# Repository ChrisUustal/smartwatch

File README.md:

# DataRacer
### A Wrist-Mounted Data Logger for Race Car Drivers
###### By Chris Uustal | Fall '21 | CE395 - Wearables & Embedded Computing
## Executive Summary:
#### Motivation: Why am I doing this? 
I'm taking a class (duh). But actually, I'm a member of the Formula SAE team here
at Northwestern University, and we've spent years collecting data on our vehicle
while never collecting data on our drivers. I wanted to change that. 
#### Problem: What am I fixing? 
Collecting meaningful data from a driver is HARD. They need to wear a very particular
racing suit and the environment they are operating in is... less than forgiving. The
solution also has to be very user friendly and reliable, because if it isn't then
they just won't use it. 
#### Solution: How am I fixing it? 
I designed a smart watch platform capable of collecting and logging sensor data that
has a simple user interface, logs data to a removable microSD card, and can be easily
scaled to include whatever sensors are needed by the driver (whenever those sensors
are back in stock). 
#### Impact: The bigger picture 
The team spends thousands of hours every year trying to tune every ounce of performance 
out of our vehicle, but the driver is picked based off knowledge--not skill. If 
we can find meaningful ways to improve the skills of our drivers based off this data,
then that could make bigger improvements to the performance of our vehicle than some 
projects ever could. 
## Design: 
#### Visual Story

#### Hardware Block Diagram

#### What parts did I use? 
- ESP32 Feather by Adafruit
- OLED 128x64 FeatherWing by Adafruit
- MicroSD Breakout Board by Adafruit
- MPU6050 9DOF+Temp I2C Sensor (unknown vendor)
- 500mAh LiPoly Battery by Adafruit
#### Implementation
###### Hardware 
The decision was made early on to use parts that were as easy as possible to get working 
out of the box with as little tinkering as possible. Both Sparkfun and Adafruit have 
fantastic development platforms for this, so I arbitrarily chose Adafruit, since they both
appeared to have similar levels of hardware diversity. With that, I immediately began 
moving forward with the Adafruit ESP32 Huzzah feather and OLED 128x32 FeatherWing as my 
MCU and interface of choice. I've worked with the ESP32 previously and was quite happy 
with its performance and feature set, so I saw no reason to reinvent the wheel. The only
major downside of the ESP32 compared to alternative options is its high power draw, but
since this design was for prototyping only, I wasn't as concerned about battery life so 
long as it doesn't completely destroy the demo experience, which ended up being a good choice. 
The OLED 128x32 FeatherWing (which I later upgraded to the 128x64 variant) offered interface
buttons and a screen for displaying information to the user, so it checked all my interface 
requirements in one package. Since all featherWings are intended to be stacking shields 
directly on top of any feather MCU, I implemented it as such, directly stacking the display
ontop of the MCU even in the final package. Conventionally the two components would be spaced 
out by male headers on the OLED plugged into female headers from the ESP32, but this takes
up a lot of vertical space within my packaging, something which was already at a premium 
in the tiny form factor I was going for. As such, in the final build I actually soldered
both the ESP32 and OLED directly to the same pair of male headers, allowing them to be stacked 
together in a package nearly 0.25 inches shorter than with conventional stacking. The
buttons integrated into the OLED directly map to GPIO ports on the ESP32, and the OLED 
gets its display information over I2C. The OLED comes with a library and tutorial out of
the box, so it was up and running in no time. 
<br /><br />
For the battery, Adafruit offers a selection of LiPoly batteries that are capable
of directly interfacing with and charging from the ESP32 feather, so I used the largest one
from their series capable of fitting into the footprint I ended up deciding on, 500mAh. I
originally worked with a 1200mAh battery, but this ended up being significantly larger than
was reasonable for a wrist-mounted device. 
<br /><br />
The MicroSD card breakout that I used was the only one Adafruit offered, so since I'd already
had good luck on their other products, I simply continued using them as my vendor of choice. 
It included 5v to 3.3v level shifting, so while that made the package a little larger, it
also protected me in case I ended up wanting to use the breakout in another design later 
on (which I didn't end up doing, but that's fine). It interfaced over SPI, which is expected
for a MicroSD card, but it also offered some nice quality of life features like card detection
and an indicator LED when it's being written to. 
<br /><br />
The only actual sensor in the device, the MPU6050 9DOF+Temp sensor I just happened to
have already in inventory, so I started testing with it originally just to have an example
sensor without the intention of actually including it in the final product. It isn't from
Adafruit and honestly I don't even know where I got it from, but it also operated off I2C 
and worked easily enough that I didn't ever have to worry about it. It was even small enough 
that it never presented any major packaging issues. 
<br /><br />
I wanted to include a lot more sensors in the design, but part shortage issues as well as
some miscommunications with the university buying some sensors for me ended up making it 
more logically to just focus on developing the backbone system and leaving more sensors 
to the future development of the solution. 
###### Software
Given that the code base for this project is well into the thousands of lines, it would be 
impossible for me to walk through all of it. Instead, I'll just give a high level overview 
of what's going on. 
<br /><br />
At startup, initialization functions for everything are called to ensure all the variables 
are properly initialized, timers are zero-ed to the current time, state machines are set
to their default state, and buttons are set to their default position. It also performs 
some preliminary checking to ensure all the devices its expecting are connected, and if not
then it makes sure to not bother trying to interface with those devices until they are connected
or the system is restarted. It also checks if an SD card is present and if the log file
is present on that SD card. If it isn't, then it creates a new one, but if it is, then it 
just opens then file and gets ready to write to it. It also does things like connect to the 
WiFi to get the current time. 
<br /><br />
After this it launches into an infinite loop of sudo-virtual timers. Essentially, when I first
designed the system, everything was simply running in the main loop. Even once I broke it out 
to make calls to these functions modular, I still had every function running every iteration of 
the loop. This is generally a terrible approach, so I designed a system that keeps track of 
the last time a loop function was called and how long it should wait until it calls it again. 
This uses millis(), an Arduino function which returns the number of milliseconds since the 
code started running, and it rolls over every 52 days or so. This allowed me to execute certain
functions (such as my button handler) significantly more often than checking the battery or 
writing to the screen, since a slow button is easily noticeable but a slowly changing battery 
percentage is hardly noticeable. The implementation isn't perfect since currently it requires
you to manually add each new looping function in the code, but I didn't end up finding the
better approach of allowing the code to dynamically add and remove functions from the list
to be worth the effort it would take to implement it. This is also blocking, meaning if one task 
hangs then the whole loop hangs, but a non-blocking implementation would require ISRs which
are more complex and approaching RTOS levels of complexity, which I was attempting to avoid here. 
<br /><br />
The display function is one of the larger components as it has to handle displaying all 
possible information to the user dynamically. This basically has one master function which
handles configuring and sending the data to the screen every frame, then there's a finite 
state machine which manages all the different screens and uses a switch statement to select 
between them, which are then broken out into a bunch of smaller helper functions. 
<br /><br />
The button handler is another massive function which manages all the interactions the user can
have with the device. Specifically, the device comes with 3 buttons plus a reset. Since the user
should really never press reset unless they have to, this leaves us with 3 interface options. 
That's not a lot, so the button handler tracks when a button is pressed and un-pressed and 
can perform different actions based on the duration of the press. My particular implementation 
works based off a simple threshold where a button pressed less than 500ms performs a "short press" 
action and another beyond that performs a "long press" action. This lets the user do something
like put the device to sleep with a long press on A but toggle between screens with a short press
on A. This works off a massive struct with a bunch of internal functions that are being called 
every loop iteration. The final sample rate for the buttons is 20ms, but this worked without 
issue at 5ms and 40ms, so I think anything in this range works fine. I should note that, since 
certain functions like the stopwatch really depend on accurate timing, I also have a separate
function which executes when the button is pressed regardless of press duration, but I avoided
this in most cases since it reduces a button to only one function. Button actions are also tied
to the current FSM state of the display with a switch statement, so a short press on C (which 
I've informally dubbed primary interaction) when on the stopwatch screen will start/stop it, 
but on the logging screen it enables/disables logging, and a similar effect occurs for every screen. 
Again, there are better ways to implement this with interrupts, but this worked and was easy. 
<br /><br />
The SD card functions are the last complicated part, but they also took the longest to debug 
and were the easiest to break. From a high level, the device starts up and checks if an SD 
card is physically present in the device. If so, then it attempts to interface with it. If that's
successful, it then checks if the log file exists on the SD card. If not, then it creates it
and puts the headers for the sensors being logged, but if it does, then it notes that a restart
was performed. Logging is disabled by default on startup, but if logging is enabled at startup, 
then it would immediately start logging all the sensor data at 100Hz. As a looping function, it 
continually checks if the SD card is present and if it should be logging data. If both of these
are true, then it logs data. If the card is present but it shouldn't be logging, then it does
nothing. If it notices that the card isn't present but it should be logging, it turns logging 
off to avoid attempting to and failing to write to the card. When it notices that a card goes
from not being inserted to being inserted, it attempts to run the setup function again to
allow the card to be connected and disconnected dynamically without powering the device off. 
However, to get the SD card to log this quickly without issue, I had to make some custom tweaks 
to the library. Particularly, the default SD library opens the file, adds the data you want to add, 
then closes the file for every bit of text you append. While this is very reliable, closing the 
file also takes ~6ms. This may not sound like much, but when we're logging 100x per second, that
quickly consumes 60% of our compute time just closing this SD file over and over. Instead of doing
that, I just open the file at startup and keep it open when logging data to it, only closing it 
when I stop logging. Because of this, if you eject the card in the middle of logging, the data
hasn't yet been fully properly saved to the card, meaning some data gets lost. To avoid this issue, 
I have a slower function running every second in the background that periodically closes and 
reopens the SD card file, saving all the data properly in the process while only wasting 6ms 
every second, which is way better! When the device goes to sleep it also closes and reopens 
the SD card just in case. 
<br /><br />
The sleep function is fairly simple, but it's still very useful. Essentially, the ESP32 is such
a powerful chip that it can actually be put to sleep in a variety of different levels to save
increasingly more power. Lower levels are more inconvenient but come at reduced power consumption. 
Since I just wanted basic sleeping functionality and a moderate amount of power savings, I used
the lightest level of sleep, actually known as "light sleep," in which the ESP32 doesn't even
lose the state of its registers and can perfectly resume operation. This brings the chip down
from about 50mA to less than 1mA of current draw according to its datasheet, and that was good 
enough for these applications. To get this to work, all you have to do is call a specific
function that puts the ESP32 to sleep and configure a specific pin to wake the chip on a rising
or falling edge. With a little display animation as it goes to sleep and wakes up, the feature
was done. 
<br /><br />
All other functions are fairly self-explanatory, but I'll give them each a quick overview:
- accel: it measures the magnitude of the current acceleration every 10ms as well as the maximum 
acceleration and lets you zero and un-zero this value dynamically. Does the same for temperature.
- battery: literally just checks the current voltage of the battery and does a rudimentary 
mapping of this value to an approximate percentage based off a chart on the internet. 
- fsm: just declares a few finite state machines which are used throughout the system, like the 
display, settings, and a few smaller ones. 
- RTC: connects to wifi and pings a server asking for the current time, then displays it back 
to the user. This isn't an actual RTC, but it can fake it with the onboard wifi. 
- settings: I started implementing a settings interface for the device near the end of the 
development cycle as it became clear that a user might want to tweak things themselves without
having to get their hands dirty in the code. It wasn't fully implemented since it ended up being
a lot more work than it was worth for a demo, but the template is there. 
- soc: daughter function set for battery. Honestly doesn't need to be its own file. 
- stopwatch: tracks a timer based on millis() that the user can start and pause dynamically. 
It could be used for tracking lap times or something like that, but a "lap" function was
never implemented. It changes formatting dynamically though to support up to 999 minutes. 
<br /><br />
That's it. There's so much more to go into in the software for a true deep dive, but this should 
be enough to give a realistic fundamental understanding of how the entire code base works together. 
###### CAD 
The packaging quickly became clear once I'd finalized the components I was using. There were very
few ways to put the components together geometrically that made any sense, so I just picked one 
and started designing a housing. Because 3D printing is an easy way to iterate quickly on a design, 
it was the clear choice for the housing. I tried both ABS and PLA, and the higher durability of PLA 
made it a clearly better choice for my applications. Since 3D printing generally doesn't like
overhangs in the designs, I split then housing into two main parts called the lower and upper
housing that then could be press fit together. It also has an opening for accessing the microUSB
port and MicroSD card slot from within the housing beyond the obvious space for the display and button
user interfaces. In the final iteration, I also added small handles on the sides so a band 
could be attached to the device, allowing it to actually be mounted to one's wrist. Below is
a picture of the full CAD assembly without the lower housing (so you can see the intended packaging):
<br />

<br />
You can then compare that to the actual packaging I constructed: 
<br />

<br />
There were a few challenges and unknowns with the housing that meant I got up to 4 iterations
on the lower and 5 iterations on the upper, but they were fairly trivial to resolve with trial and
error. For example, I originally made the inner dimensions of the housing the exact outer dimensions
of the components, but plastic actually expands a little when you print it, so I had to increase my 
inner dimensions by a tiny bit to fit the components comfortably. Similarly, getting elements like
standoffs that mate to the mounting holes on the display as well as the wall thickness just right
took a few tries, but eventually it got to the current design which works well enough. 
#### Pictures
It would be better suited to a video, but here are some pictures of it in action: 
<br />
Acceleration: 
<br />

<br />
Temperature: 
<br />

<br />
Stopwatch: 
<br />

<br />
Clock: 
<br />

<br />
Battery Percentage: 
<br />

<br />
Logging: 
<br />

<br />
Settings: 
<br />

<br />
#### Lessons Learned
1. Once you've got a basic idea of the direction you want to go in, just start moving. 
The easiest way to run out of time and kill a design is by not giving yourself
as much time as possible with the hardware. The sooner you have it in your hands 
and either get something working or realize that it's way too hard and you need 
to change direction the better. The biggest thing that killed the momentum in this
project was waiting for components to be ordered that never arrived. Burn the money, 
but the components, get them here tomorrow and start working immediately. It's worth it. 
2. When you're coding, steal as much as possible. Someone else already did something 
kind of similar? Cool, don't reinvent the wheel. Build something cooler off the back 
of what they already did rather than wasting time doing the same thing. If you're 
writing official code for a company, that's something different, but the gloves come off 
when you're just prototyping alone, and the only goal is to produce something that works
as fast as possible by any means necessary. 
3. Always have multiple parts of a project that could use improvement--it avoids blockers. 
It might seem good to really focus in on one particular element of a project and polish 
it to completion, but that's terrible for prototyping, because sometimes things get stuck. 
Sometimes things don't work or they get stuck or you get frustrated or shipping takes 2 weeks. 
Rather than having nothing to do for that time, always have another direction to start
developing in, so when that blocker becomes unblocked you have something fresh to pivot back to. 
4. (If you really want to try this yourself) Packaging a wearable is *very* hard. 
Everyone you show it to is going to expect it to be this slim, tiny little magic device
that is *not* prototype friendly at all. What I have right now works fine, but if you want
to take this any further than I already have, then wait until after the global chip shortage, 
design a custom debug-friendly PCB, and then you might have something people will
actually want to look at. An 18mm thicc watch is *not* attractive. 
## Non-Class Things:  
#### Will I support this project? 
No, don't assume I will. I might update it in the future, and if so, cool! But 
I also might not, so don't hold your breath. 
#### Can you use this? 
Of course, everything is open source and you're free to use it for your own personal non-commercial
projects. If you want to use it to start a company or sell a product or something, shoot 
me a message and I'm sure we can work something out.

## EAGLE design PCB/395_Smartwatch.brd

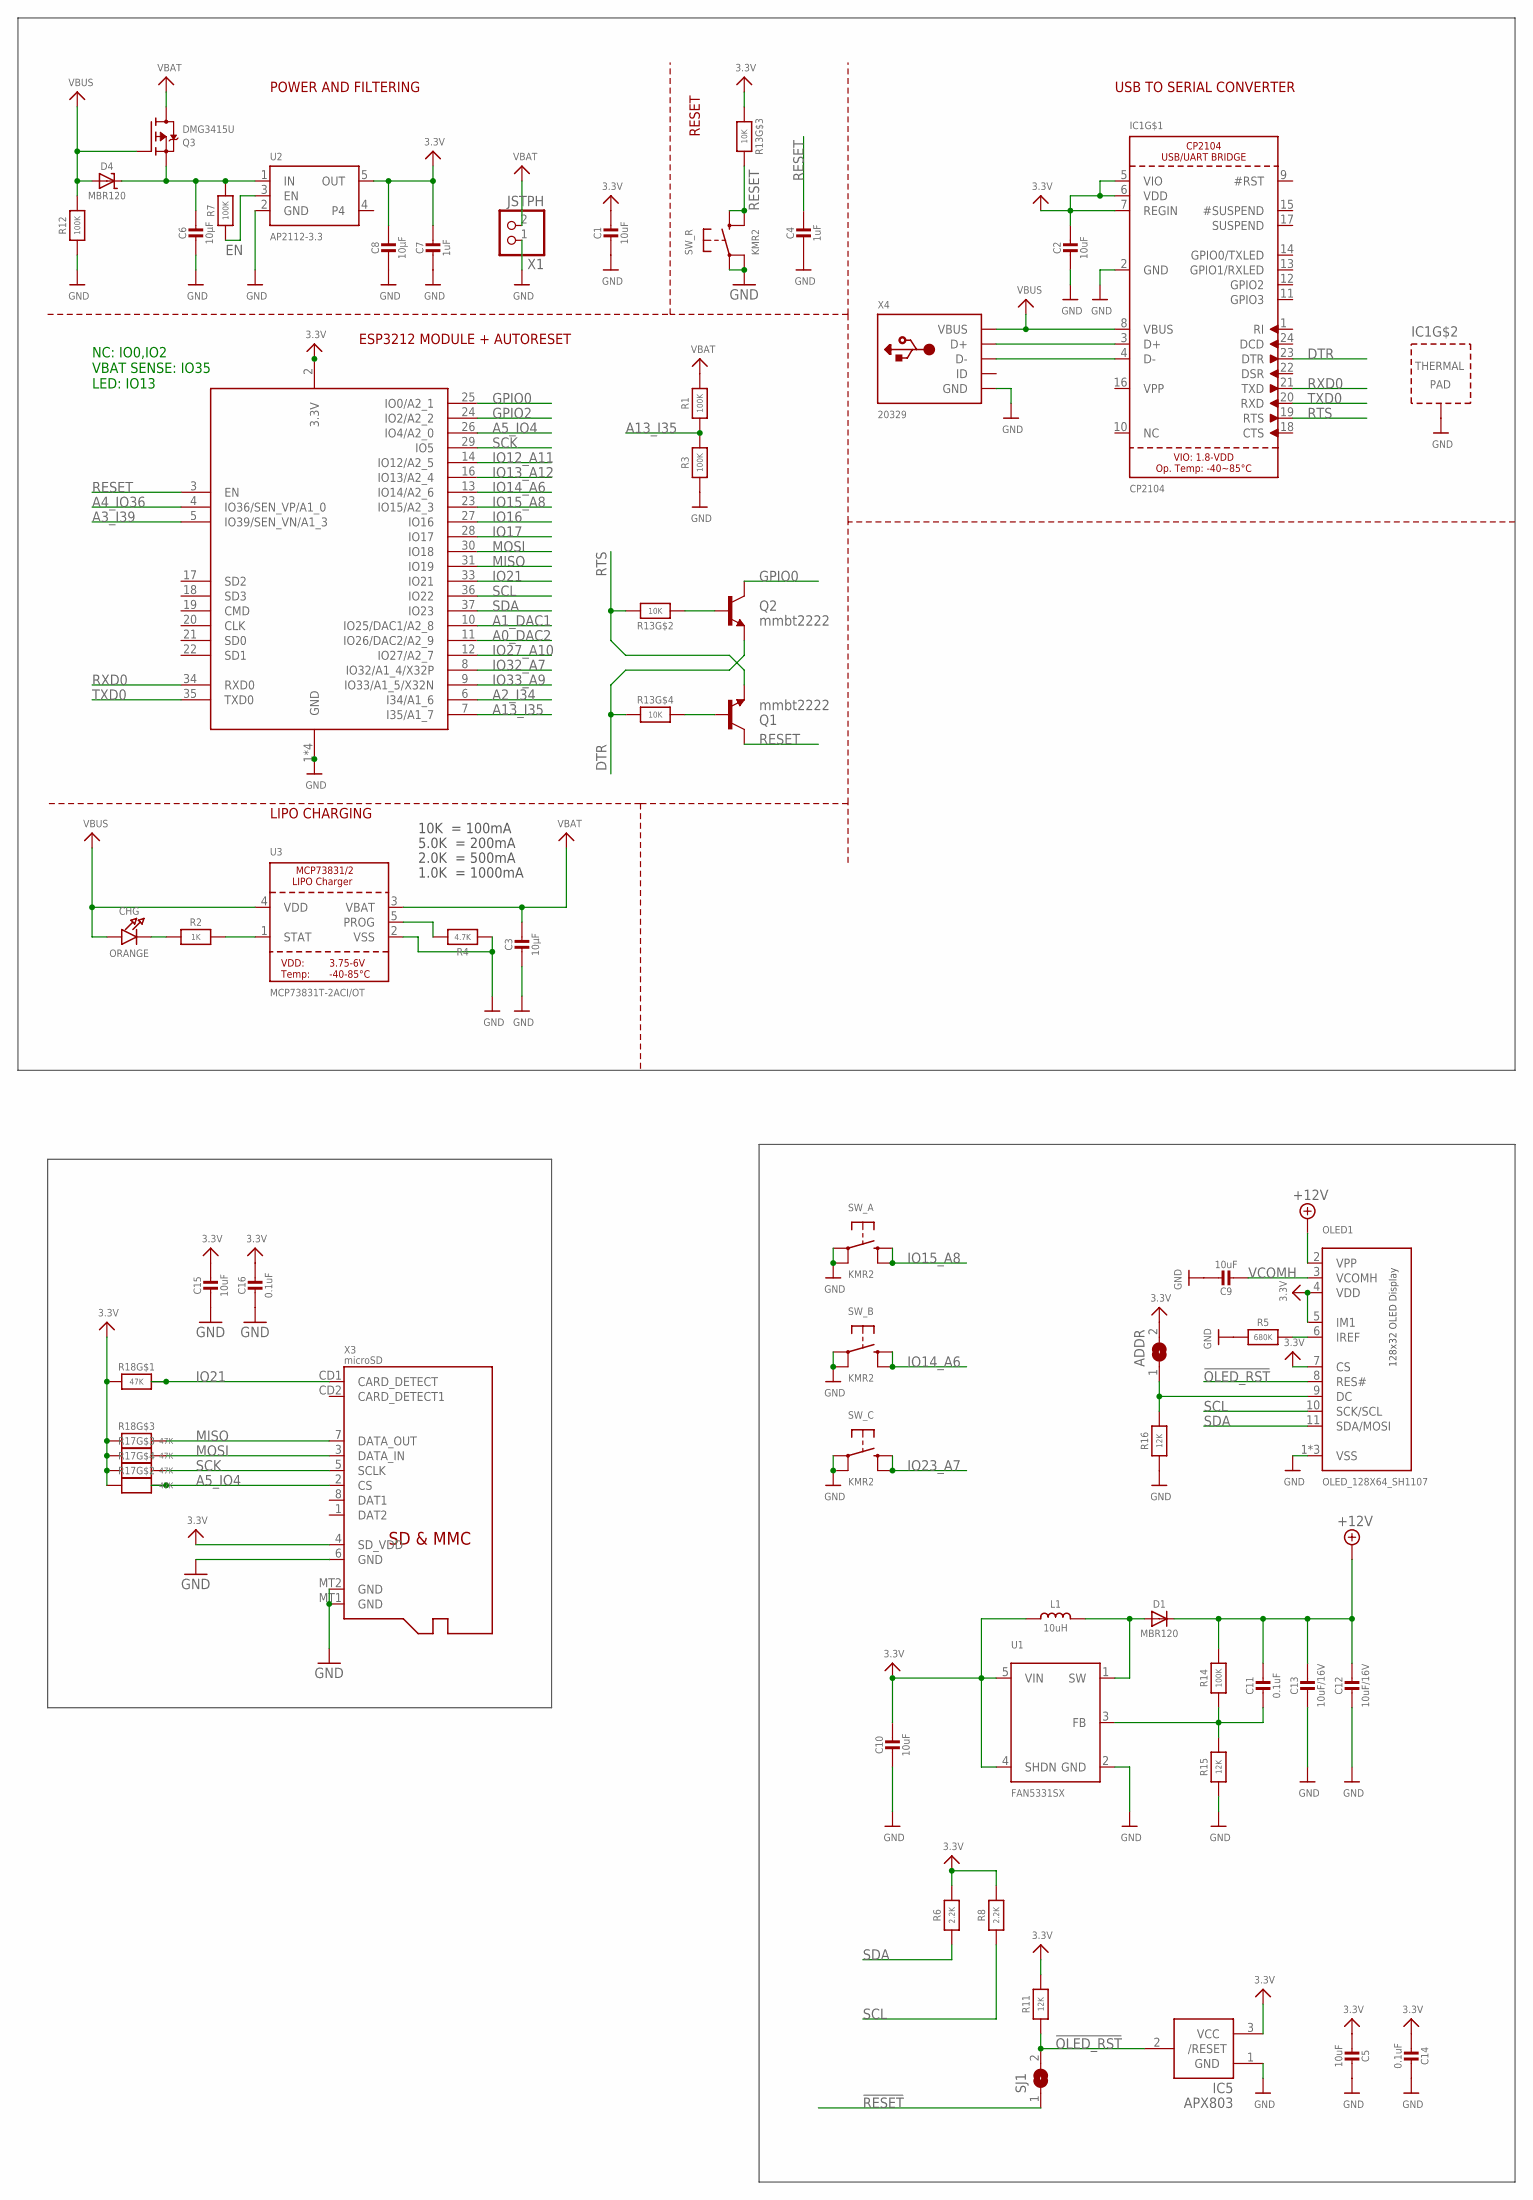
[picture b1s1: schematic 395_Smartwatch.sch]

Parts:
ADDR: SOLDERJUMPER; SOLDERJUMPER_ARROW_NOPASTE
C1, C2, C5, C9, C10, C15: 10uF; 0805-NO
C3, C6, C8: 10µF; 0805-NO
C4, C7: 1uF; 0603-NO
C11, C14, C16: 0.1uF; 0603-NO
C12, C13: 10uF/16V; 0805-NO
CHG: ORANGE; CHIPLED_0805_NOOUTLINE
D1, D4: MBR120; SOD-123
IC1: CP2104; QFN24_4MM_SMSC
IC5: APX803; SOT23
L1: 10uH; INDUCTOR_1007
OLED1: OLED_128X64_SH1107; QT1107P11A
Q1, Q2: mmbt2222; SOT23-3
Q3: DMG3415U; SOT23-R
R1, R3, R7, R12, R14: 100K; 0603-NO
R2: 1K; 0603-NO
R4: 4.7K; 0603-NO
R5: 680K; 0603-NO
R6, R8: 2.2K; 0603-NO
R11, R15, R16: 12K; 0603-NO
R13: 10K; RESPACK_4X0603
R17, R18: 47K; RESPACK_4X0603
SJ1: SOLDERJUMPERCLOSED; SOLDERJUMPER_CLOSEDWIRE
SW_A: KMR2; BTN_KMR2_4.6X2.8
SW_B: KMR2; BTN_KMR2_4.6X2.8
SW_C: KMR2; BTN_KMR2_4.6X2.8
SW_R: KMR2; BTN_KMR2_4.6X2.8
U1: FAN5331SX; SOT23-5
U2: AP2112-3.3; SOT23-5
U3: MCP73831T-2ACI/OT; SOT23-5
X1: JSTPH; JSTPH2
X2: ESP32_WROOM32_SKINNY; WROOM32_SKINNY
X3: microSD; MICROSD
X4: 20329; 4UCONN_20329_V2

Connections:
3.3V: ADDR.2, C1.1, C2.1, C5.2, C7.1, C8.1, C10.1, C14.2, C15.1, C16.1, IC1.5 (VIO), IC1.6 (VDD), IC1.7 (REGIN), IC5.3 (VCC), L1.P$1 (1), OLED1.4 (VDD), OLED1.5 (IM1), OLED1.7 (CS), R6.2, R8.2, R11.2, R13.3 (1), R17.2 (1), R17.3 (1), R17.4 (1), R18.1, R18.3 (1), U1.4 (SHDN), U1.5 (VIN), U2.5 (OUT), X2.2 (3.3V), X3.4 (SD_VDD); also elsewhere on the board
!OLED_RST: IC5.2 (/RESET), OLED1.8 (RES#), R11.1, SJ1.2
!RESET: SJ1.1
+12V: C11.1, C12.1, C13.1, D1.C, OLED1.2 (VPP), R14.2
A0_DAC2: X2.11 (IO26/DAC2/A2_9)
A1_DAC1: X2.10 (IO25/DAC1/A2_8)
A2_I34: X2.6 (I34/A1_6)
A3_I39: X2.5 (IO39/SEN_VN/A1_3)
A4_IO36: X2.4 (IO36/SEN_VP/A1_0)
A5_IO4: R17.7 (2), X2.26 (IO4/A2_0), X3.2 (CS)
A13_I35: R1.1, R3.2, X2.7 (I35/A1_7)
DTR: IC1.23 (DTR), Q2.2 (E), R13.4 (1)
EN: R7.1, U2.3 (EN)
GND: C1.2, C2.2, C3.2, C4.2, C5.1, C6.2, C7.2, C8.2, C9.1, C10.2, C12.2, C13.2, C14.1, C15.2, C16.2, IC1.2 (GND), IC1.THERM (TP), IC5.1 (GND), OLED1.1 (VSS), OLED1.12 (VSS), OLED1.13 (VSS), R3.1, R4.1, R5.1, R12.1, R15.1, R16.1, SW_A.A, SW_A.A' (P1), SW_B.A, SW_B.A' (P1), SW_C.A, SW_C.A' (P1), SW_R.A, SW_R.A' (P1), U1.2 (GND), U2.2 (GND), U3.2 (VSS), X1.1, X2.1 (GND), X2.15 (GND), X2.38 (GND), X2.P$1 (GND), X3.6 (GND), X3.MT1 (GND), X3.MT2 (GND), X4.BASE@1 (GND), X4.BASE@2 (GND), X4.GND, X4.SPRT@1 (GND), X4.SPRT@2 (GND), X4.SPRT@3 (GND), X4.SPRT@4 (GND); also elsewhere on the board
GPIO0: Q2.3 (C), X2.25 (IO0/A2_1)
GPIO2: X2.24 (IO2/A2_2)
IO12_A11: X2.14 (IO12/A2_5)
IO13_A12: X2.16 (IO13/A2_4)
IO14_A6: SW_B.B (S), SW_B.B' (S1), X2.13 (IO14/A2_6)
IO15_A8: SW_A.B (S), SW_A.B' (S1), X2.23 (IO15/A2_3)
IO16: X2.27 (IO16)
IO17: X2.28 (IO17)
IO21: R18.8 (2), X2.33 (IO21), X3.CD1 (CARD_DETECT)
IO23_A7: SW_C.B (S), SW_C.B' (S1)
IO27_A10: X2.12 (IO27/A2_7)
IO32_A7: X2.8 (IO32/A1_4/X32P)
IO33_A9: X2.9 (IO33/A1_5/X32N)
MISO: R18.6 (2), X2.31 (IO19), X3.7 (DATA_OUT)
MOSI: R17.6 (2), X2.30 (IO18), X3.3 (DATA_IN)
unnamed: CHG.C, R2.1
unnamed: IC1.3 (D+), X4.D+
unnamed: R2.2, U3.1 (STAT)
unnamed: R4.2, U3.5 (PROG)
unnamed: IC1.4 (D-), X4.D-
unnamed: C6.1, D4.C, Q3.2 (S), R7.2, U2.1 (IN)
unnamed: OLED1.6 (IREF), R5.2
unnamed: D1.A, L1.P$2 (2), U1.1 (SW)
unnamed: C11.2, R14.1, R15.2, U1.3 (FB)
unnamed: ADDR.1, OLED1.9 (DC), R16.2
unnamed: Q1.1 (B), R13.5 (2)
unnamed: Q2.1 (B), R13.2 (1)
RESET: C4.1, Q1.3 (C), R13.6 (2), SW_R.B (S), SW_R.B' (S1), X2.3 (EN)
RTS: IC1.19 (RTS), Q1.2 (E), R13.7 (2)
RXD0: IC1.21 (TXD), X2.34 (RXD0)
SCK: R17.5 (2), X2.29 (IO5), X3.5 (SCLK)
SCL: OLED1.10 (SCK/SCL), R8.1, X2.36 (IO22); also elsewhere on the board
SDA: OLED1.11 (SDA/MOSI), R6.1, X2.37 (IO23); also elsewhere on the board
TXD0: IC1.20 (RXD), X2.35 (TXD0)
VBAT: C3.1, Q3.3 (D), R1.2, U3.3 (VBAT), X1.2
VBUS: CHG.A, D4.A, IC1.8 (VBUS), Q3.1 (G), R12.2, U3.4 (VDD), X4.VBUS
VCOMH: C9.2, OLED1.3 (VCOMH)

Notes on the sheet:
POWER AND FILTERING
RESET
10K = 100mA
5.0K = 200mA
2.0K = 500mA
1.0K = 1000mA
USB TO SERIAL CONVERTER
LIPO CHARGING
ESP3212 MODULE + AUTORESET
NC: IO0,IO2 VBAT SENSE: IO35 LED: IO13

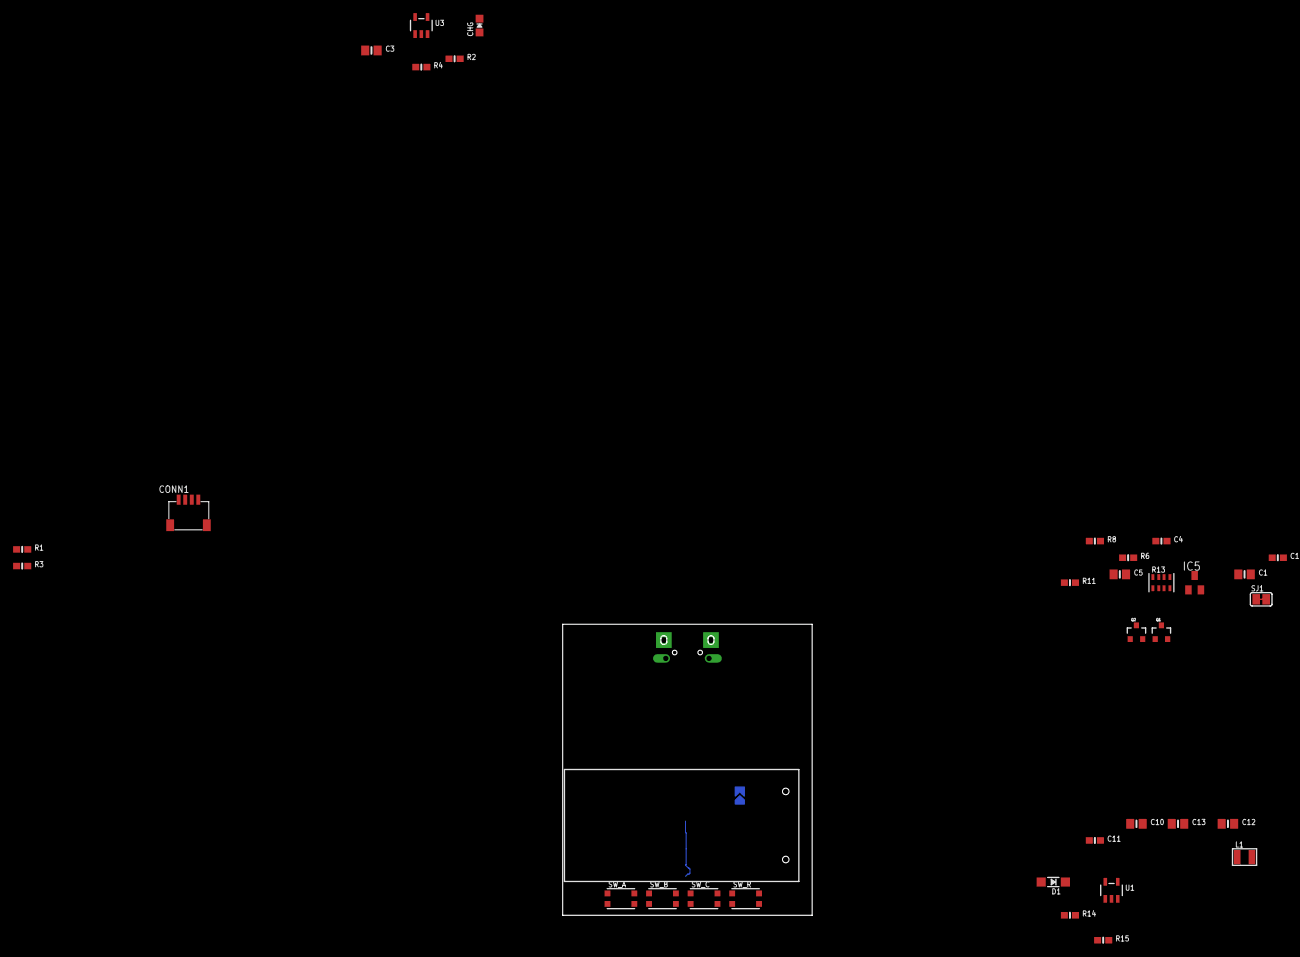
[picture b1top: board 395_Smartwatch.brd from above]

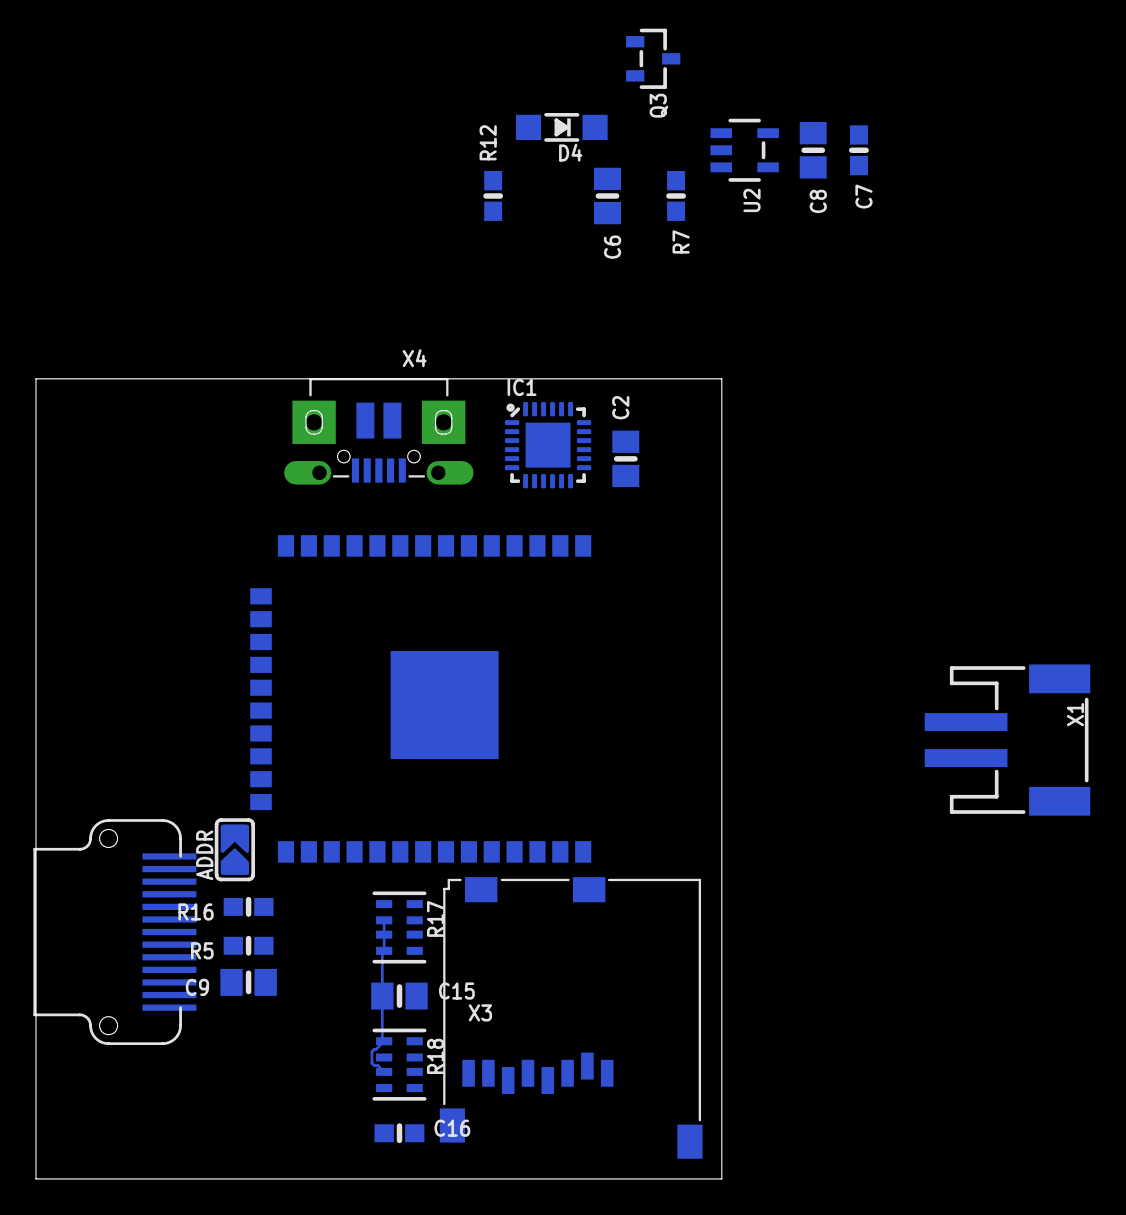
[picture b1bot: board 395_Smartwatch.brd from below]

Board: 2 copper layers, 38.1 x 44.5 mm, 56 parts (22 on the bottom side), 37 nets.

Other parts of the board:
CONN1: STEMMA_I2C_QT; JST_SH4

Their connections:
3.3V: CONN1.2; also elsewhere on the board
GND: CONN1.1, CONN1.MT1, CONN1.MT2; also elsewhere on the board
SCL: CONN1.4; also elsewhere on the board
SDA: CONN1.3; also elsewhere on the board

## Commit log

2021-11-24 Uploaded initial files
2021-11-24 Making a folder
2021-11-24 fixed file structure, added readme
2021-11-24 changed readme to .md
2021-11-24 updated readme again
2021-11-24 more readme stuff
2021-11-24 added pcb files
2021-11-24 periodic SD save (10s)
2021-11-26 added tons
2021-11-26 fixing readme for class
2021-11-26 more readme
2021-11-26 upgraded readme
2021-11-26 bruh so much readme stuff
2021-11-28 added backlog
2021-11-29 updated backlog, added settings menu, added variable text size
2021-11-29 added support for 128x64 OLED
2021-11-29 added cad
2021-11-30 start w/o sensors connected, updated bat% display
2021-11-30 revised ToS
2021-12-01 demo build
2021-12-01 added demo build schematic
2021-12-01 added project title and info in main
2021-12-01 fixed sleep text size issue
2021-12-07 updating readme
2021-12-07 added visual story img
2021-12-07 readme hardware implementation
2021-12-07 more readme software stuff
2021-12-08 readme cad + pics
2021-12-08 fixed img link
2021-12-08 added pic links
2021-12-09 video tweaks
2021-12-09 added more pics
2021-12-09 formatting

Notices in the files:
parts and their libraries:
microbuilder: This work is placed in the public domain, and may be freely used for commercial and non-commercial work with the following conditions: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
SparkFun: Licensing: CC v3.0 Share-Alike You are welcome to use this library for commercial purposes.
